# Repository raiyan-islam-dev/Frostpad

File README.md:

# Frostpad

My submission for Hack Club's Hackpad mission on Stardance. A 6-key macropad with a rotary encoder, built around a Seeed XIAO RP2040.

## What it does

Six keys mapped to the number row by default, plus a rotary encoder for volume up, volume down and mute. The keycaps and the encoder knob are both my own designs, modeled to fit standard MX switches and an EC11 encoder shaft.

## Schematic

The switches are wired directly to the XIAO, no diode matrix. I had enough GPIO pins for it (6 switches plus 3 pins for the encoder), so I kept it simple instead of adding a matrix I didn't need.

## PCB

Two layer board, 74mm by 69mm. Laid out the switches in a 3x2 grid with the encoder above them.

## Case

The case is two printed parts: a tray that holds the PCB and a tilted pedestal underneath it, so the board sits angled toward you instead of flat on the desk. No top plate, the switches sit exposed.

## Bill of materials

| Part | Qty | Notes |
|---|---|---|
| Seeed XIAO RP2040 | 1 | main MCU |
| MX-style mechanical switch | 6 | |
| EC11 rotary encoder w/ push switch | 1 | |
| Custom PCB | 1 | see `PCB/` |
| Printed tray | 1 | see `production/frostpad_tray.step` |
| Printed pedestal | 1 | see `production/frostpad_pedestal.step` |
| Printed keycap x6 | 6 | see `production/frostpadkeycap.step` |
| Printed encoder knob | 1 | see `production/frostpadvolumeknowb.step` |
| M3 screws | 4 | mounting holes |

## Firmware

Written in KMK, CircuitPython based. Lives in `Firmware/main.py`. Switches on D0 through D5, encoder A/B on D8/D7, encoder push on D9.

## Files

- `CAD/` - full assembled model
- `PCB/` - KiCad project, schematic, board
- `Firmware/` - main.py
- `production/` - gerbers, drill file, case and part STEP files for printing/fab

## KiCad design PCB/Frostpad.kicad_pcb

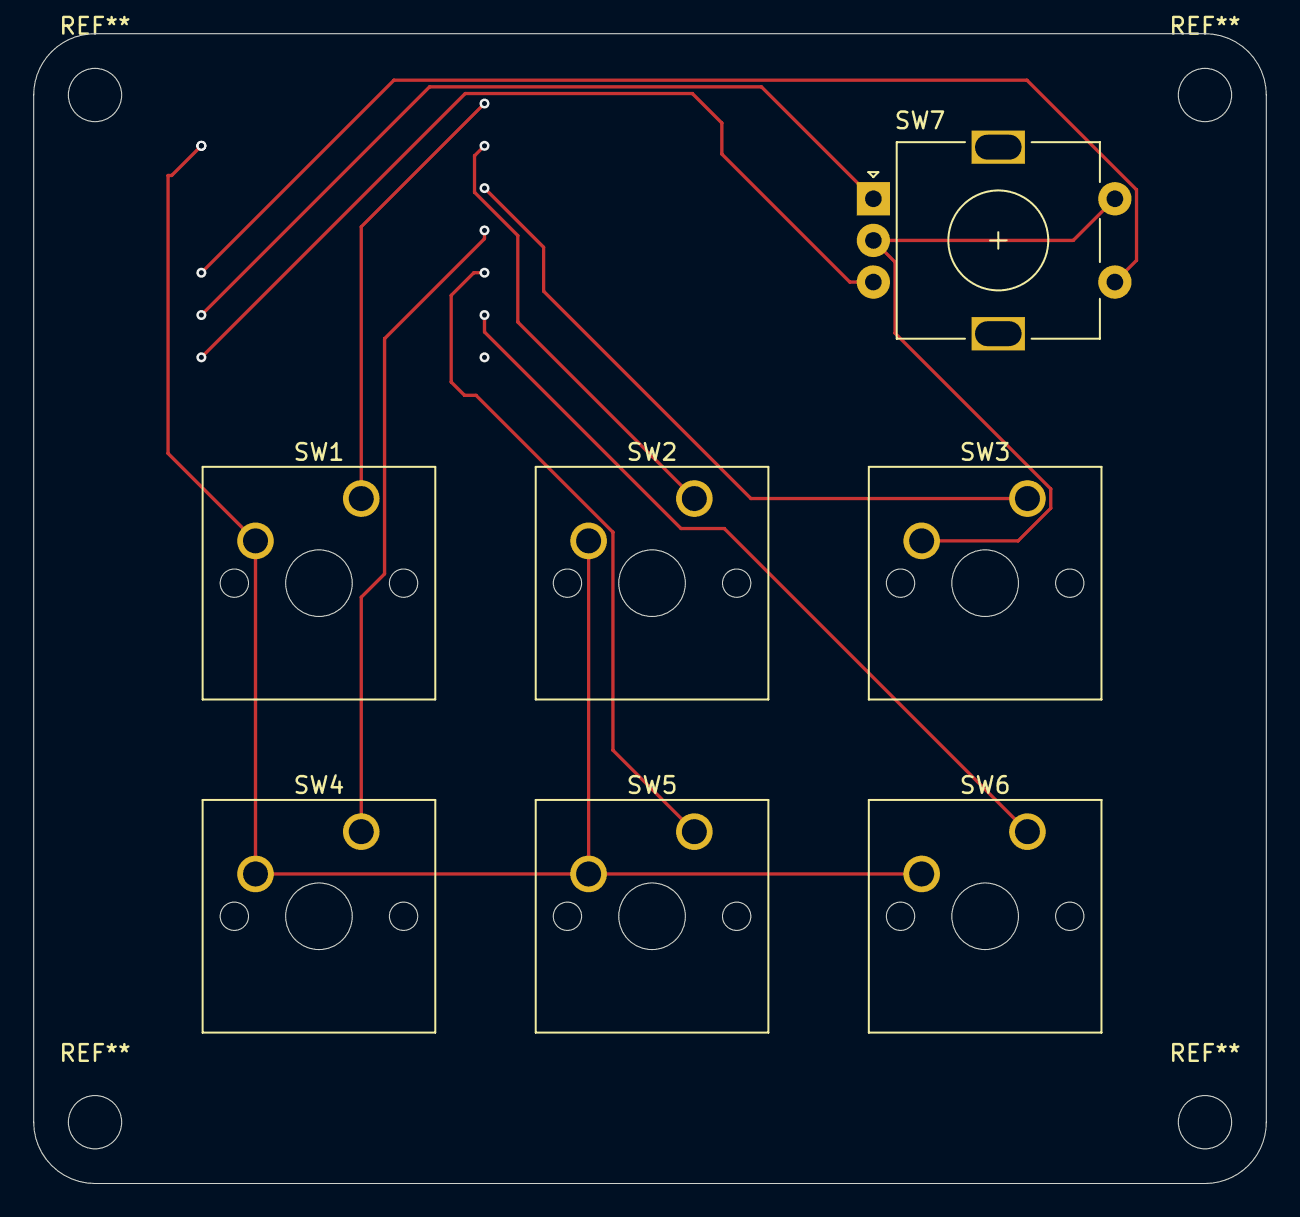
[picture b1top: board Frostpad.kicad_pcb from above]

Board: 2 copper layers, 74.0 x 69.0 mm, 8 parts (1 on the bottom side), 10 nets.

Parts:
SW1, SW2, SW3, SW4, SW5, SW6: SW_Push; SW_Cherry_MX_1.00u_PCB
SW7: RotaryEncoder_Switch; RotaryEncoder_Alps_EC11E-Switch_Vertical_H20mm
U1: MOUDLE-SEEEDUINO-XIAO; MCU_Seeed_ESP32C3

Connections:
unnamed: SW1.2, SW2.2, SW3.2, SW4.2, SW5.2, SW6.2, SW7.C, SW7.S2, U1.13 (GND)
unnamed: SW1.1, U1.1 (PA02_A0_D0)
unnamed: SW2.1, U1.2 (PA4_A1_D1)
unnamed: SW7.S1, U1.10 (PA5_A9_D9_MISO)
unnamed: SW7.A, U1.9 (PA7_A8_D8_SCK)
unnamed: SW5.1, U1.5 (PA8_A4_D4_SDA)
unnamed: SW6.1, U1.6 (PA9_A5_D5_SCL)
unnamed: SW3.1, U1.3 (PA10_A2_D2)
unnamed: SW4.1, U1.4 (PA11_A3_D3)
unnamed: SW7.B, U1.8 (PB09_A7_D7_RX)
